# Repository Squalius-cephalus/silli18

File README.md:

# Silli18
RP2040 based macropad, which uses [QMK](https://github.com/qmk/qmk_firmware) firmware with [Vial](https://get.vial.today/) support. 

If you are interested in macropad with hotswap sockets, check [Silakka18](https://github.com/Squalius-cephalus/silakka18).

## Bill of materials

 - 1 x PCB
 - 1 x Pin compatible Raspberry Pi Pico
 - 1 x 3D printed bottom plate
 - 1 x 3D printed top plate
 - 2 x EC11 Rotary encoders
 - 16 x MX style mechanical switches
 - 16 x MX compatible keycaps
 - 18 x 1N4148 diode
 - 8 x M2 4mm bolt
 - 8 x M2 brass inserts 
 - 8x Rubber feet

## TODO

 1. Make build guide

PCB design uses footprints from [ScottoKeebs](https://github.com/joe-scotto/scottokeebs/tree/main/Extras/ScottoKicad "ScottoKeebs") and [kbd library.](https://github.com/foostan/kbd "kbd library.")

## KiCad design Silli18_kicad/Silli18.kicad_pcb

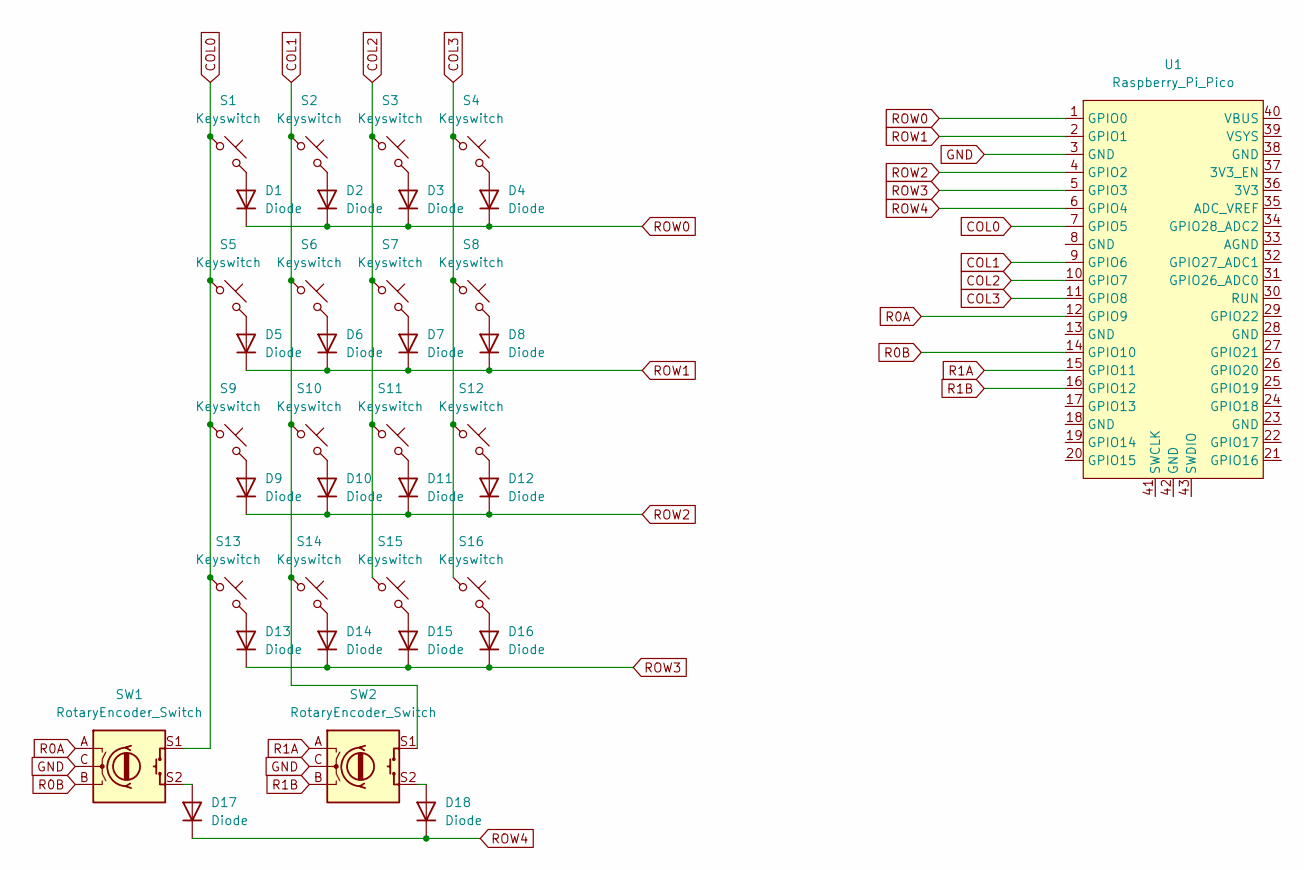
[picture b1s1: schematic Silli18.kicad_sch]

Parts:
D1, D2, D3, D4, D5, D6, D7, D8, D9, D10, D11, D12, D13, D14, D15, D16, D17, D18: Diode; D3_TH
S1, S2, S3, S4, S5, S6, S7, S8, S9, S10, S11, S12, S13, S14, S15, S16: Keyswitch; MX_PCB_1.00u
SW1, SW2: RotaryEncoder_Switch; RotaryEncoder_EC11
U1: Raspberry_Pi_Pico

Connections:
COL0: S1.1, S5.1, S9.1, S13.1, SW1.S1, U1.7 (GPIO5)
COL1: S2.1, S6.1, S10.1, S14.1, SW2.S1, U1.9 (GPIO6)
COL2: S3.1, S7.1, S11.1, S15.1, U1.10 (GPIO7)
COL3: S4.1, S8.1, S12.1, S16.1, U1.11 (GPIO8)
GND: SW1.C, SW2.C, U1.3 (GND)
unnamed: D1.2 (A), S1.2
unnamed: D2.2 (A), S2.2
unnamed: D3.2 (A), S3.2
unnamed: D4.2 (A), S4.2
unnamed: D5.2 (A), S5.2
unnamed: D6.2 (A), S6.2
unnamed: D7.2 (A), S7.2
unnamed: D8.2 (A), S8.2
unnamed: D9.2 (A), S9.2
unnamed: D10.2 (A), S10.2
unnamed: D11.2 (A), S11.2
unnamed: D12.2 (A), S12.2
unnamed: D13.2 (A), S13.2
unnamed: D14.2 (A), S14.2
unnamed: D15.2 (A), S15.2
unnamed: D16.2 (A), S16.2
unnamed: D17.2 (A), SW1.S2
unnamed: D18.2 (A), SW2.S2
R0A: SW1.A, U1.12 (GPIO9)
R0B: SW1.B, U1.14 (GPIO10)
R1A: SW2.A, U1.15 (GPIO11)
R1B: SW2.B, U1.16 (GPIO12)
ROW0: D1.1 (K), D2.1 (K), D3.1 (K), D4.1 (K), U1.1 (GPIO0)
ROW1: D5.1 (K), D6.1 (K), D7.1 (K), D8.1 (K), U1.2 (GPIO1)
ROW2: D9.1 (K), D10.1 (K), D11.1 (K), D12.1 (K), U1.4 (GPIO2)
ROW3: D13.1 (K), D14.1 (K), D15.1 (K), D16.1 (K), U1.5 (GPIO3)
ROW4: D17.1 (K), D18.1 (K), U1.6 (GPIO4)

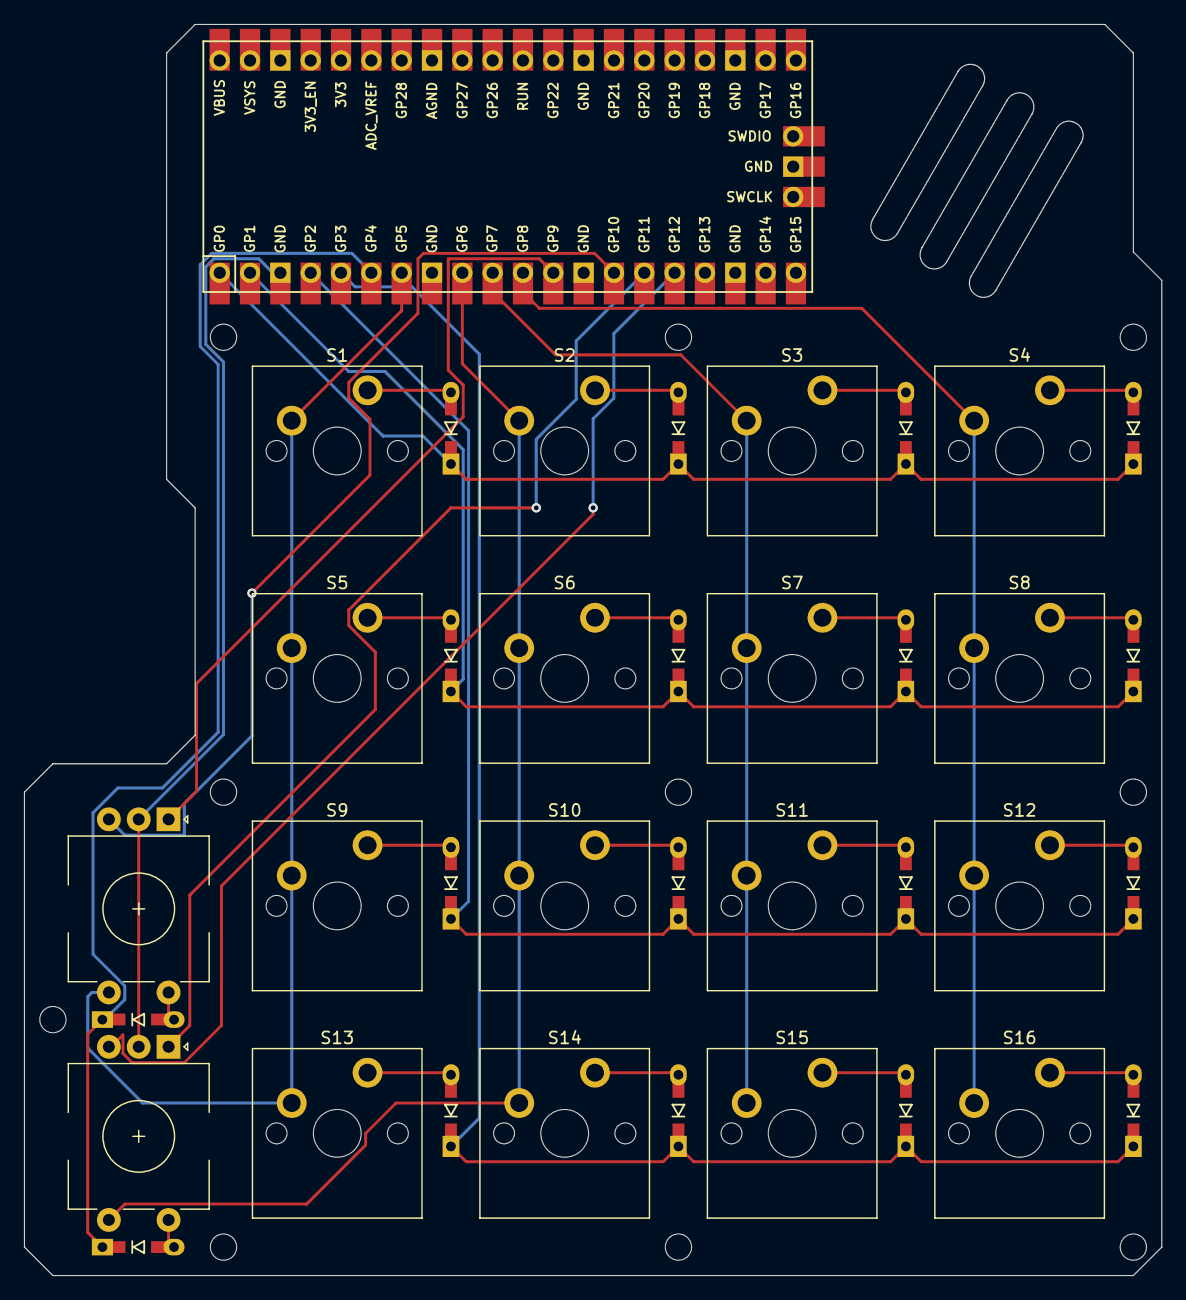
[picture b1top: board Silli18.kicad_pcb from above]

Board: 2 copper layers, 95.2 x 104.8 mm, 37 parts (0 on the bottom side), 32 nets.

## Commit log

2024-03-17 Added STL and gerber files
2024-03-20 Updated README and new picture
2024-03-20 Firmware added and prebuild Vial firmware too.
2024-03-25 Added KiCAD files
2024-03-25 Fixed STL files scale.
2024-05-23 Update README.md
    Fixed BOM
